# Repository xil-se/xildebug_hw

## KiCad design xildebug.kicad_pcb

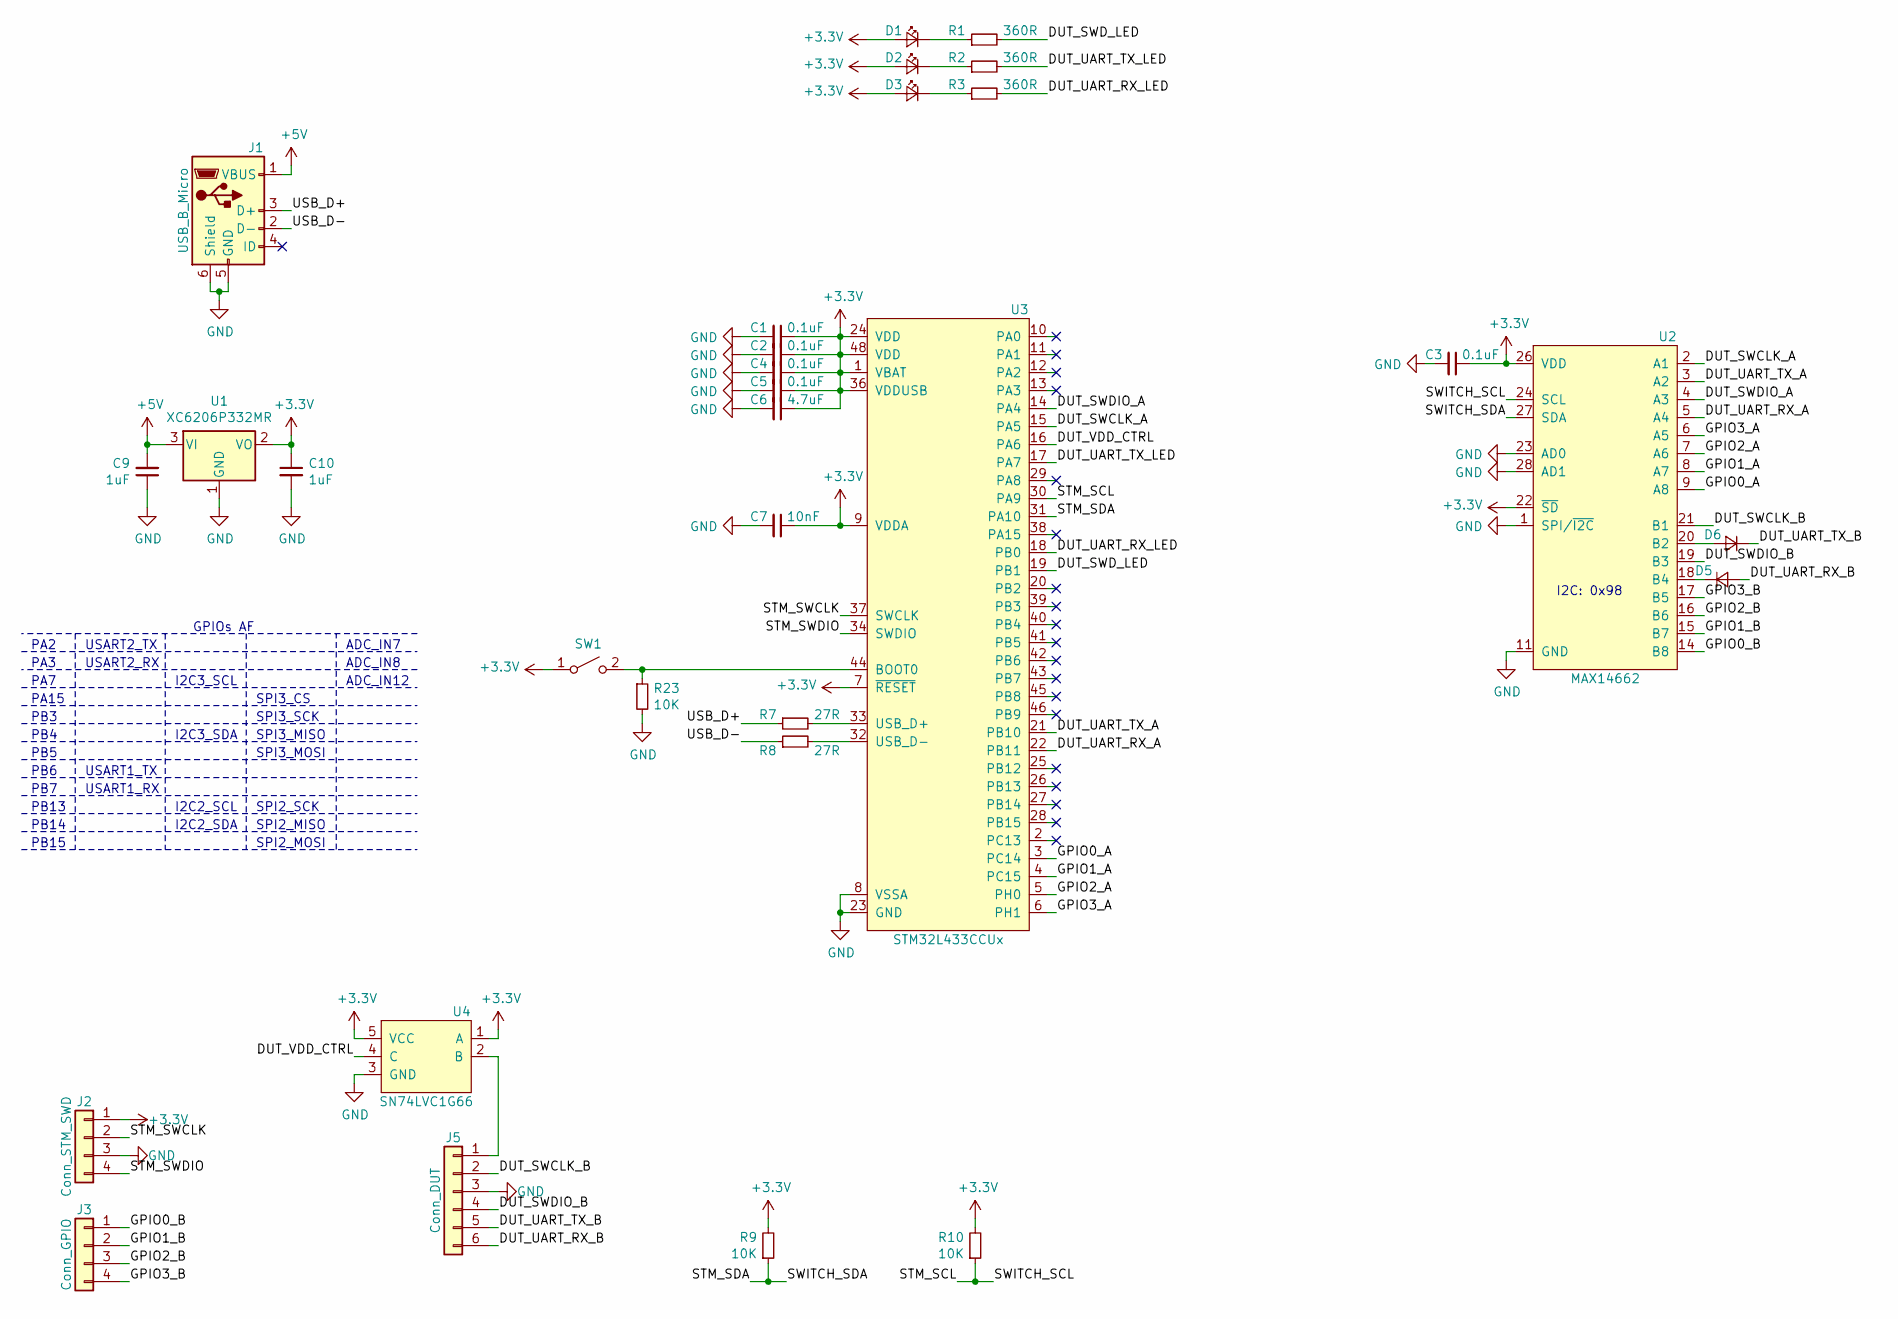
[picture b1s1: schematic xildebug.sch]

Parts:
C1, C2, C3, C4, C5: 0.1uF; C_0603_1608Metric
C6: 4.7uF; C_0603_1608Metric
C7: 10nF; C_0603_1608Metric
C9, C10: 1uF; C_0603_1608Metric
D1, D2, D3: DUT_UART_TX_LED; LED_0603_1608Metric
D5: D_TX; D_SOD-323_HandSoldering
D6: D_RX; D_SOD-323_HandSoldering
J1: USB_B_Micro; USB_Micro-B_Molex-105017-0001
J2: Conn_STM_SWD; JST_SH_BM04B-SRSS-TB_1x04-1MP_P1.00mm_Vertical
J3: Conn_GPIO; PinHeader_1x04_P2.54mm_Vertical
J5: Conn_DUT; PinHeader_1x06_P2.54mm_Vertical
R1, R2, R3: 360R; R_0603_1608Metric
R7, R8: 27R; R_0603_1608Metric
R9, R10, R23: 10K; R_0603_1608Metric
SW1: BOOT0; SW_SPST_B3U-1000P
U1: XC6206P332MR; SOT-23
U2: MAX14662; QFN-28-1EP_4x4mm_P0.4mm_EP2.4x2.4mm
U3: STM32L433CCUx; QFN-48-1EP_7x7mm_P0.5mm_EP5.15x5.15mm
U4: SN74LVC1G66; SC-70-5

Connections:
+3V3: C1.1, C2.1, C3.1, C4.1, C5.1, C6.1, C7.1, C10.1, D1.2 (A), D2.2 (A), D3.2 (A), J2.1, R9.2, R10.2, SW1.1 (A), U1.2 (VO), U2.22 (~SD~), U2.26 (VDD), U3.1 (VBAT), U3.7 (~RESET~), U3.9 (VDDA), U3.24 (VDD), U3.36 (VDDUSB), U3.48 (VDD), U4.1 (A), U4.5 (VCC)
+5V: C9.2, J1.1 (VBUS), U1.3 (VI)
/DUT_SWCLK_A: U2.2 (A1), U3.15 (PA5)
/DUT_SWCLK_B: J5.2, U2.21 (B1)
/DUT_SWDIO_A: U2.4 (A3), U3.14 (PA4)
/DUT_SWDIO_B: J5.4, U2.19 (B3)
/DUT_SWD_LED: R1.2, U3.19 (PB1)
/DUT_UART_RX_A: U2.5 (A4), U3.22 (PB11)
/DUT_UART_RX_B: D5.2 (A), J5.6
/DUT_UART_RX_LED: R3.2, U3.18 (PB0)
/DUT_UART_TX_A: U2.3 (A2), U3.21 (PB10)
/DUT_UART_TX_B: D6.1 (K), J5.5
/DUT_UART_TX_LED: R2.2, U3.17 (PA7)
/DUT_VDD_CTRL: U3.16 (PA6), U4.4 (C)
/GPIO0_A: U2.9 (A8), U3.3 (PC14)
/GPIO0_B: J3.1, U2.14 (B8)
/GPIO1_A: U2.8 (A7), U3.4 (PC15)
/GPIO1_B: J3.2, U2.15 (B7)
/GPIO2_A: U2.7 (A6), U3.5 (PH0)
/GPIO2_B: J3.3, U2.16 (B6)
/GPIO3_A: U2.6 (A5), U3.6 (PH1)
/GPIO3_B: J3.4, U2.17 (B5)
/STM_SCL: R10.1, U2.24 (SCL), U3.30 (PA9)
/STM_SDA: R9.1, U2.27 (SDA), U3.31 (PA10)
/STM_SWCLK: J2.2, U3.37 (SWCLK)
/STM_SWDIO: J2.4, U3.34 (SWDIO)
/USB_D+: J1.3 (D+), R7.1
/USB_D-: J1.2 (D-), R8.1
GND: C1.2, C2.2, C3.2, C4.2, C5.2, C6.2, C7.2, C9.1, C10.2, J1.5 (GND), J1.6 (Shield), J2.3, J5.3, R23.2, U1.1 (GND), U2.1 (SPI/~I2C~), U2.11 (GND), U2.23 (AD0), U2.25 (GND), U2.28 (AD1), U2.29 (GND), U3.8 (VSSA), U3.23 (GND), U3.35 (GND), U3.47 (GND), U4.3 (GND)
unnamed: D1.1 (K), R1.1
unnamed: D2.1 (K), R2.1
unnamed: D3.1 (K), R3.1
unnamed: D5.1 (K), U2.18 (B4)
unnamed: D6.2 (A), U2.20 (B2)
unnamed: J5.1, U4.2 (B)
unnamed: R7.2, U3.33 (USB_D+)
unnamed: R8.2, U3.32 (USB_D-)
unnamed: R23.1, SW1.2 (B), U3.44 (BOOT0)

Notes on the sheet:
GPIOs AF
PA2
PA3
PA7
PA15
PB3
PB4
PB5
PB7
PB13
PB14
PB15
USART2_TX
USART2_RX
PB6
USART1_TX
USART1_RX
I2C3_SCL
I2C3_SDA
I2C2_SCL
I2C2_SDA
SPI3_CS
SPI3_SCK
SPI3_MISO
SPI3_MOSI
SPI2_SCK
SPI2_MISO
SPI2_MOSI
ADC_IN7
ADC_IN8
ADC_IN12
I2C: 0x98

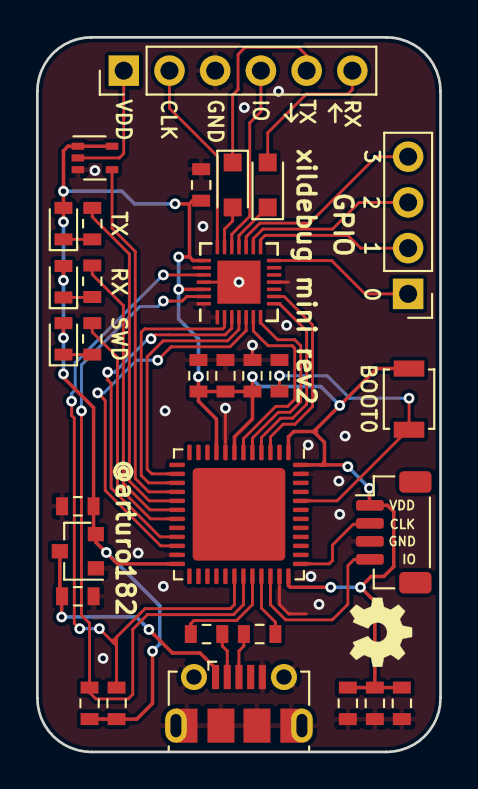
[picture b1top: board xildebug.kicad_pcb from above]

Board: 2 copper layers, 22.4 x 39.7 mm, 31 parts (0 on the bottom side), 38 nets.

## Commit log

2018-03-29 Initial import, WIP
2018-03-29 Update footprints to nightly
2018-03-30 More work on the schematic
    Replaced the STM chip with one that has more GPIO
    Added decoupling to STM
    Moved VDD circuitry to separate sheet
    Added RGB LED
2018-03-30 Update sub-schematic pin directions
2018-03-30 Changed the USB data pin names to match the USB connector convention
2018-04-02 Add ferrite bead on the VDDA of the STM
2018-04-02 Add footprint for the STM that works for QFN and QFP
2018-04-04 Route the PCB
2018-04-05 Add DUT silk
2018-04-08 Add button on BOOT0
2018-04-21 Last touch-up for the production, add gerber files
2018-10-31 Minification
2018-11-29 rev2
    - Replaced the VDD mosfet with a analog switch
    - Changed footprint of STM32L433 to standard one
    - Moved UART to USART3, same as xildebug big
